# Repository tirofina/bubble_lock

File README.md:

# Privacy Bubble Keyring

![Story page 1. 4:30 PM, Mom heads out for a walk. Her daughter calls from work: "Mom, where are you?" "At the park. Get back to work." Mom pushes away a GPS watch: "Am I a prisoner?" The daughter shows her the keyring instead: "Who sees my walks?" "No one. It only shows home or away. Press orange if you get lost."](docs/story/page-1.png)

![Story page 2. Two weeks later, the daughter's screen shows only "4:31 PM, Mom went out" and "5:36 PM, Mom came home." At 5:09 PM Mom stands at a fork in the park path: "I know this path..." At 5:13 PM the daughter gets a check-in: "4 min at the east fork. Try calling. View for 5 min," and Mom presses the orange PANIC button. On a park bench, Mom says "Your dad and I used to sit here." "I know." Location sharing turns off.](docs/story/page-2.png)

*The keyring's family story, pages 1 and 2.*

**Privacy by default. Help before the button.** A BLE keyring for an older parent who lives alone, built on the [oneM2M](https://www.onem2m.org) service layer and ETSI MEC.

Mobius4 oneM2M CSE (4.24.5 in test runs, 4.25.0 on the team server) | ETSI MEC Sandbox | Code Apache-2.0 | Docs and hardware CC BY 4.0 | 2026 oneM2M International Hackathon

| | |
|---|---|
| Hackster.io project | [Privacy Bubble: Help Before the Button](https://www.hackster.io/even-bubble-lock-is-rock/privacy-bubble-help-before-the-button-601c1d) |
| Demo video (under 5 minutes) | [Mom, Where Are You? on YouTube](https://www.youtube.com/watch?v=vOgl1aOGWl0) |
| Why oneM2M, feature by feature | [docs/oneM2M-why.md](docs/oneM2M-why.md) |
| Architecture, resource tree, protocols | [docs/architecture.md](docs/architecture.md) |

## What it does

A resident carries the keyring, her daughter acts as guardian, and a caregiver visits in the afternoon. The oneM2M CSE stores shared data and enforces access for every app. The integration service adds grants, consent and approvals. Together they enforce four rules:

1. **Presence by default.** The keyring reports presence and button presses over BLE to a Raspberry Pi Gateway, which writes them to the CSE. The guardian sees one coarse status: At Home, Moving or In Park.
2. **Devices on grant.** A command requires an active, time-bounded grant and completes when the device reports a matching readback of its physical output.
3. **Help before the button.** A routine model learns her usual walks. On an unusual evening, a Claude triage agent sends the guardian a check-in message before the resident presses PANIC.
4. **Location on approval.** Precise location remains encrypted and becomes visible to one recipient for one incident, for up to five minutes.

*The guardian's alert card shows the triage agent's 17:13 check-in, the PANIC press escalating the same alert at 17:18, and a five-minute location share. Captured live from a real Mobius4 CSE with simulated device positions.*

## Architecture

```mermaid
flowchart LR
  K["Keyring r26<br/>ESP32-S3, BLE"] -- "BLE, bonded" --> GW["Raspberry Pi Gateway<br/>SQLite outbox"]
  GW -- "oneM2M MQTT binding, HTTPS fallback<br/>TLS 1.3 mTLS" --> CSE["Mobius4 CSE<br/>AE, container, flexContainer,<br/>group, subscription, ACP"]
  CSE -- "m2m:sgn" --> APPS["Guardian, caregiver and<br/>operator apps"]
  CSE -- "m2m:sgn" --> AI["Routine AE and triage AE<br/>MCP servers, Claude Code"]
  IPE["oneM2M MEC IPE<br/>on mep1, moves to mep2"] -- "oneM2M" --> CSE
  MEC["ETSI MEC Sandbox<br/>MEC011, 012, 013, 021"] --- IPE
  FL["Federated learning<br/>coordinator and workers"] -- "oneM2M" --> CSE
```

| oneM2M feature | Use here |
|---|---|
| accessControlPolicy | Every app, the MEC IPE and the AI agent are originators with narrow rights; each client certificate maps to one originator |
| Subscription and notification | One write notifies every subscribed app |
| Group and fanOutPoint | One UPDATE reaches every member keyring, with a result per member |
| SDT (TS-0023) and flexContainer | Device state is a `binarySwitch` (`cod:binSh`), found by `cnd` discovery; the keyring maps to `deviceServiceButton` with `pushButton` and `battery` ([model](docs/keyring-sdt-model.md)) |
| container and contentInstance | Immutable observations, receipts and incidents with an expiry |
| IPE | MEC013 Location, MEC012 RNIS and MEC021 events become oneM2M resources |

We map the edge layout to deployment option B of oneM2M TR-0077: the CSE and the MEC platform run on separate edge nodes.

## Results

Local runs use real Mobius4 processes (4.24.5, and 4.25.0 for the access-control matrix); the team server runs Mobius4 4.25.0. Every receipt identifies its simulated components. `npm run verify` passes 13 steps with 686 tests ([log](docs/verification/2026-11-22/results.json)).

| What | Result | Setup | Receipt |
|---|---|---|---|
| Keyring → Pi → Mobius4 | 35 real BLE observations stored and read back; 15/15 delivered over HTTPS during a broker outage | Real hardware | [pi-cse](keyring/evidence/2026-11-10-pi-cse/README.md) |
| Command with readback | LED ON and OFF commands settled after GPIO readback arrived through a CSE notification | Real hardware | [LED](keyring/evidence/2026-11-11-scoped-feather-led/receipt.json) |
| PANIC to three apps | 10–12 ms, 19/19 checks passed | Real CSE, emulated keyrings | [multiapp](docs/verification-evidence/2026-11-19/multiapp-real-cse.json) |
| One tap, three keyrings | `fopt` returned 2004, 2004 and 4103; retry targeted the member with 4103; 27/27 checks passed | Real CSE | [group command](docs/verification-evidence/2026-11-19/group-command-real-cse.json) |
| MQTT first, HTTPS when needed | All 509 observations arrived across 4 fault conditions | Real Gateway daemon | [protocol matrix](docs/verification-evidence/2026-11-19/protocol-matrix-real-cse.json) |
| Access-control matrix | 838/838 cases passed for six roles and six operations, including subscription creation and revocation | Mobius4 4.25.0 | [acp](docs/verification-evidence/2026-11-21/acp-real-cse.json), [location privacy](docs/verification-evidence/2026-11-21/location-privacy-real-cse.json) |
| Identity bound to ACP | 918/918 security cases passed; a forged originator received 4103 | Two real CSEs, real PKI | [acp-mtls](docs/verification-evidence/2026-11-19/acp-mtls-real-cse.json) |
| CSE handover | 30 handovers between two hosts preserved all 2,337 observations; p95 interruption was 978.4 ms; an unapproved originator received 4103 after every handover | Mobius4 4.25.0 on a PC and on a VM | [two hosts](docs/verification-evidence/2026-11-23/handover-two-host-real-cse.json), [one host](docs/verification-evidence/2026-11-19/handover-auto-real-cse.json) |
| MEC IPE | 33/33 checks passed on the real ETSI MEC Sandbox; relocation from mep1 to mep2 passed 25/25 checks and preserved every event | Real sandbox, scripted movement | [sandbox](docs/verification-evidence/2026-11-20/mec-ipe-sandbox.json), [day of care](docs/verification-evidence/2026-11-20/mec-day-of-care.json) |
| Check-in before PANIC | Across 6 synthetic walks: 0 false alarms, 0 missed events and a 265 s lead for the fork anomaly; the five-minute dwell baseline produced 12 false alarms | Real sandbox and CSE, synthetic walks | [triage](docs/verification-evidence/2026-11-20/anomaly-triage.json) |
| Federated learning | Macro-F1 reached 0.9394 versus 0.9479 for centralized training; raw data stayed local; the team server CSE completed 6 rounds | Real CSE, synthetic data | [local](docs/verification-evidence/2026-11-19/fl-onem2m-real-cse.json), [server](docs/verification-evidence/2026-11-20/fl-server-cse.json) |
| Team server CSE | The sandbox IPE wrote MEC locations over mTLS and passed all 11 checks reached during the run; the receipt records the remaining walk, RNIS, renewal and teardown checks as pending | Real sandbox, real server CSE | [server IPE](docs/verification-evidence/2026-11-20/mec-ipe-server-cse.json) |

Per-package notes are in [docs/rubric-work](docs/rubric-work), and every receipt is in [docs/verification-evidence](docs/verification-evidence).

## Hardware

| Part | Details |
|---|---|
| Keyring r26 | 4-layer ESP32-S3 board with 47 factory-assembled top-side parts, 1.54-inch ST7789 LCD, confirm and PANIC buttons, and a 1,000 mAh Li-Po. Gerber, BOM, CPL and KiCad project: [keyring/pcb/r26](keyring/pcb/r26/README.md) |
| Case | 11-part PLA print with STEP, STL and 3MF files and an assembly guide: [keyring/case/r26](keyring/case/r26/README.md) |
| Gateway | Raspberry Pi Zero 2 W with BlueZ: [raspberry-pi-gateway](keyring/raspberry-pi-gateway/README.md) |
| Bench keyring | Adafruit Feather ESP32 V2 for the command path: [feather_probe](keyring/firmware/feather_probe/README.md) |
| Full design | r18, with fuel gauge, accelerometer, charger and audio: [keyring/pcb/r18](keyring/pcb/r18/README.md) |

The r26 firmware (`keyring_r26_front_st7789` in [platformio.ini](keyring/firmware/platformio.ini)) and its bring-up guide ([R26_BRING_UP.md](keyring/pcb/R26_BRING_UP.md)) are in this repository.

## Quick start

Requires Node.js 22.19 or newer, Python 3.11 or newer, and OpenSSL. On Windows, clone with LF line endings so that the oneM2M XSD hashes match.

```powershell
git clone -c core.autocrlf=false https://github.com/tirofina/bubble_lock
cd bubble_lock
$env:PYTHON = (py -3 -c "import sys; print(sys.executable)")   # Linux: export PYTHON=python3
npm run setup     # installs pc-mobius, web-dashboard and the Python test environment
npm run verify    # 13 steps: unit tests, XSD closure, contracts, oneM2M dry-run, demo, replay, web build
```

Run the demo, event server, and dashboard in three terminals:

```powershell
npm run demo                  # writes pc-mobius/receipts/integration-demo.jsonl
$env:RECEIPT_FILE = (Resolve-Path 'pc-mobius/receipts/integration-demo.jsonl').Path
npm run events                # SSE event server on 127.0.0.1:4174
npm run dashboard             # http://127.0.0.1:5173
```

## Real Mobius4 and ETSI MEC Sandbox runs

Get [Mobius4](https://github.com/IoTKETI/mobius4) 4.24.5 (`git checkout v4.24.5`, `npm ci`) and set `MOBIUS4_ROOT`. Run PostgreSQL 17 with PostGIS and write `.local/postgres/connection.json` with `host`, `port`, `user`, `password` and `database`. The CORE contract runs against a CSE started by `pc-mobius/scripts/start-mobius4-test.ps1`; every other runner starts its own CSE processes and writes a JSON receipt.

| Result | Command |
|---|---|
| CORE contract on one CSE | `node pc-mobius/scripts/run-contract.mjs` after `start-mobius4-test.ps1` |
| Group fan-out and SDT clients | `node pc-mobius/scripts/run-group-command-real.mjs` |
| MQTT / HTTPS matrix | `node pc-mobius/scripts/run-protocol-matrix-real.mjs` |
| Three apps on one CSE | `node pc-mobius/scripts/run-multiapp-real.mjs` |
| Identity bound to ACP | `node pc-mobius/scripts/run-acp-mtls-real.mjs` |
| CSE handover | `node pc-mobius/scripts/run-handover-auto-real.mjs --rounds 5` |
| Federated learning | `node pc-mobius/scripts/run-fl-onem2m-real.mjs` |
| MEC IPE, local simulator | `node pc-mobius/scripts/run-mec-ipe-real.mjs` |
| MEC IPE, real sandbox | `npm --prefix pc-mobius run integration:mec-ipe-sandbox` |
| Day of care, IPE relocation | `npm --prefix pc-mobius run integration:mec-day-of-care` |
| Check-in before PANIC | `node pc-mobius/scripts/run-anomaly-triage.mjs --agent=claude` (or `--agent=scripted`) |

The sandbox runs require a local ETSI MEC Sandbox; [deploy/mec-sandbox](deploy/mec-sandbox/README.md) records the installation step by step.

## Deployment

- **Raspberry Pi Gateway:** systemd service under its own user, with certificates in `/etc/privacy-bubble/tls`: [raspberry-pi-gateway](keyring/raspberry-pi-gateway/README.md).
- **Central server:** Mobius4 with PostgreSQL and PostGIS, the binarySwitch specialization (`prepare-specialization`) and the standard subscription procedure on Mobius4 4.25.0 ([CSE_SECURITY.md](pc-mobius/integration/CSE_SECURITY.md)). The stack also includes an MQTT broker with TLS 1.3 and per-Gateway ACLs ([dev stack](keyring/dev/mobius4/README.md)), the integration API ([Gateway registration](pc-mobius/integration/GATEWAY_REGISTRATION.md)) and web apps with an OIDC backend ([oidc-session.md](web-dashboard/docs/oidc-session.md)).
- **ETSI MEC Sandbox and the MEC IPE image:** [deploy/mec-sandbox](deploy/mec-sandbox/README.md).

Certificates, private keys, passkeys, databases and runtime state belong in git-ignored paths such as `.local/` and `/etc/privacy-bubble/`.

## Repository map

| Path | Contents |
|---|---|
| [`pc-mobius/`](pc-mobius/README.md) | Central Node.js package: oneM2M core (group fan-out, SDT adapter, Gateway bridge), integration service (API, policy, MEC IPE, handover, FL, routine model, MCP servers), contracts, runners and tests |
| [`keyring/`](keyring/README.md) | Device side: firmware, PCB r18 and r26, case, Raspberry Pi Gateway, dev CSE stack, hardware evidence |
| [`web-dashboard/`](web-dashboard/README.md) | Guardian, caregiver and operator apps (React, Vite) with an SSE and OIDC backend |
| [`deploy/mec-sandbox/`](deploy/mec-sandbox/README.md) | ETSI MEC Sandbox install record, day-of-care scenario, MEC IPE container image |
| [`contracts/keyring/`](contracts/keyring/README.md) | JSON Schema contracts shared by firmware and Gateway |
| [`tests/integration/`](tests/integration) | Cross-runtime tests: Python and Node TLS 1.3 mTLS, OIDC, Gateway API |
| [`docs/`](docs) | Architecture, oneM2M rationale, per-package notes, verification logs and receipts |

Detailed design notes and run records are in Korean: [development record](docs/development-completion.md), [integration contracts](docs/branch-integration.md), and the README of each package.

## License and team

Code: [Apache License 2.0](LICENSE). Documentation, images, evidence and hardware design files: [CC BY 4.0](LICENSE-docs). Third-party material keeps its own terms: [NOTICE](NOTICE).

Team "Even Bubble lock is rock" built this project for the 2026 oneM2M International Hackathon across four roles: PC-MOBIUS-CORE, PC-MOBIUS-INTEGRATION, KEYRING and WEB-DASHBOARD. The [Hackster.io project](https://www.hackster.io/even-bubble-lock-is-rock/privacy-bubble-help-before-the-button-601c1d) lists the team members. Questions and feedback: [GitHub issues](https://github.com/tirofina/bubble_lock/issues).

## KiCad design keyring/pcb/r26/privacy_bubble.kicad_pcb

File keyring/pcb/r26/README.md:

# Keyring PCB r26 (front-side assembly)

r26 is the board revision inside the demo keyrings of Privacy Bubble Keyring. It is a 4-layer, 1.0 mm board around an ESP32-S3-WROOM-1 module, derived from r25 with one change: R71 is removed and the LCD data/command line is routed directly. For the 2026 oneM2M International Hackathon we ordered 5 boards and had 2 of them factory-assembled on the top side only.

The hardware author's original notes (Korean) are in [README.ko.md](README.ko.md). The case and its assembly guide are in [keyring/case/r26](../../case/r26/README.md).

## What is on the demo boards

| Item | Value |
|---|---|
| Stackup | 4 copper layers, 1.0 mm, standard 0.3 mm vias |
| Top side | 47 parts in 25 BOM lines, all placed by the factory; 0 hand-soldered parts, 0 jumper wires |
| Back side | 89 optional parts left unpopulated ([DNP_LIST.csv](assembly/DNP_LIST.csv)) |
| r26 change | R71 symbol, footprint and silkscreen removed; LCD_DC runs from GPIO8 (U1 pad 12) to J3 pin 6 on a 0.15 mm top-layer trace, with 0 extra vias |
| Kept from r25 | Placement, power loops, decoupling, board outline, case mounting holes and port positions |
| Checks (hardware author, KiCad 10.0.3) | DRC 0, ERC 0, unconnected 0, schematic parity 0 ([validation_summary.json](checks/validation_summary.json)) |

### Four 0-ohm bypass resistors

R72 to R75 are YAGEO RC0805JR-070RL (LCSC C96345, 0805), four per board. They let the front-side build run without the back-side power circuits.

| Resistor | Connects | Bypasses |
|---|---|---|
| R72 | VBAT to SYS_LIMIT | U3 charge and power path, U11 main switch |
| R73 | VBAT to PWR_SW (slide switch ON) | U10 undervoltage control |
| R74 | REG_EN (slide switch COM) to REG_READY (U4 EN) | U17 supply supervisor |
| R75 | +3V3 to AUX3V3 | U13 auxiliary power switch |

To populate a back-side circuit, first remove the bypass resistor that covers it. A full back-side build removes all four ([BYPASS_CONFIGURATION.csv](assembly/BYPASS_CONFIGURATION.csv)).

### Connections used by the demo firmware

| Function | Pins |
|---|---|
| Battery | J2 (check polarity first); DTP803040 1000 mAh, charged in an external 1-cell charger. USB-C charging, temperature and undervoltage circuits stay idle on this build, and USB-C carries ESP32 USB data. |
| Power switch | J9.1 ON, J9.2 COM, J9.3 OFF/GND |
| LCD (1.54 inch 240x240 ST7789) | MOSI GPIO38, SCK GPIO39, CS GPIO18, DC GPIO8, RESET GPIO43, backlight GPIO2 (HIGH off, LOW on) |
| Buttons | Confirm GPIO6, PANIC GPIO7, LOW when pressed |
| USB | D- GPIO19, D+ GPIO20, USB console. UART0 TX logging stays off because GPIO43 is the LCD reset. |
| Idle in the demo firmware | Audio, sensors, microSD, fuel gauge and the MAIN/AUX FAULT logic |

LCD harness (JST SH 8-pin) from the module labels to J3:

| LCD label | GND | VCC | SCL | SDA | RST | DC | CS | BL |
|---|---|---|---|---|---|---|---|---|
| r26 J3 pin | 2 | 1 | 4 | 3 | 7 | 6 | 5 | 8 |

Firmware build profiles, first power-on and over-the-air updates: [R26_BRING_UP.md](../R26_BRING_UP.md) and [R26_OTA.md](../../firmware/R26_OTA.md).

## Files

| Path | Contents |
|---|---|
| `privacy_bubble.kicad_pro`, `.kicad_sch`, `.kicad_pcb`, `.kicad_dru`, `fp-lib-table`, `sym-lib-table`, `Release.kicad_sym` | KiCad 10 project |
| `Sourced_4L.pretty/`, `Sourced.pretty/`, `HandSolder.pretty/`, `3dmodels/`, `sourced_cad/` | Footprints and 3D models; third-party terms in [NOTICE](../../../NOTICE) |
| [`fabrication/privacy_bubble_r26_4L_front_assembly_gerber_drill.zip`](fabrication/privacy_bubble_r26_4L_front_assembly_gerber_drill.zip) | Gerber and drill: 4 copper layers, masks and silkscreens on both sides, outline, top paste, PTH and NPTH drill |
| [`assembly/BOM_JLCPCB.csv`](assembly/BOM_JLCPCB.csv), [`assembly/CPL_JLCPCB.csv`](assembly/CPL_JLCPCB.csv) | Top-side assembly files with LCSC part numbers; quantities are per board |
| [`assembly/POPULATION_BY_REFERENCE.csv`](assembly/POPULATION_BY_REFERENCE.csv) | Populated or unpopulated, per reference |
| [`assembly/FIRMWARE_PIN_MAP.csv`](assembly/FIRMWARE_PIN_MAP.csv) | ESP32-S3 pads, nets and GPIOs used by the r26 firmware |
| `checks/validation_summary.json`, `drc_final.json`, `erc_final.json` | Hardware author's checks, KiCad 10.0.3 |
| `checks/drc_r26_label_2026-11-20.json`, `erc_r26_label_2026-11-20.json` | Re-run after the label update below, KiCad 10.0.4 |
| [`3d/r26_top_assembly.step`](3d/r26_top_assembly.step) | Board as assembled (top side) |
| [`3d/r26_aux_optional.step`](3d/r26_aux_optional.step) | Board with the optional AUX parts, for enclosure checks |
| [`exports/r26-schematic.pdf`](exports/r26-schematic.pdf) | Schematic |
| [`exports/r26-board-top.png`](exports/r26-board-top.png) | Top-side render |
| [`exports/r26-board-bottom-full-design.png`](exports/r26-board-bottom-full-design.png) | Bottom render of the full design; on the demo boards these 89 back-side parts stay unpopulated |

A KiCad XML netlist is easy to regenerate with `kicad-cli sch export netlist --format kicadxml privacy_bubble.kicad_sch`; it records the absolute path of the machine that exports it, so the repository leaves it out.

## Label update on 2026-11-20

The title blocks still named older revisions, so we changed three text fields to r26. Circuits, footprints, copper, masks, silkscreen and drill data stay the same, and the Gerber zip is the hardware author's original.

| File | Field | Before | After |
|---|---|---|---|
| `privacy_bubble.kicad_pcb` | title block rev | r19 / standard vias | r26 / direct LCD DC, front-side assembly |
| `privacy_bubble.kicad_sch` | title block rev | r17 edge ports / two-layer layout in progress | r26 / direct LCD DC, front-side assembly |
| `privacy_bubble.kicad_sch` | comment 1 | R16/R17/J8 removed; D2/R18 retained; 3D views updated | R71 removed; LCD_DC wired directly from GPIO8 to J3.6 |

| File | SHA-256 before (equal to validation_summary.json) | SHA-256 after |
|---|---|---|
| `privacy_bubble.kicad_pcb` | `3c408eef457f7f8830f5e8cf06486eea775e83996467143cab9025f8d674c1ef` | `2f1782920fe6bb1137ad30dc8b9f60af697f21621363e861de8cd5ab4229f0f4` |
| `privacy_bubble.kicad_sch` | `325c5987df2d07763a71aed6f76833c1f18a5b041ecb8c4495e2a1bf22ffe083` | `cce052aa005f6ac1cde41344dfae172f60b53c5b6fa131db039f051e661b30e7` |

Re-run with `kicad-cli` 10.0.4, errors and warnings included: DRC 0 violations and 0 unconnected items, ERC 0 violations.

## Build one

1. Order the board from the Gerber zip (4 layers, 1.0 mm) with top-side assembly from the BOM and CPL.
2. Print and assemble the case: [keyring/case/r26](../../case/r26/README.md).
3. Flash `keyring_r26_front_st7789` and pair the keyring with the Raspberry Pi Gateway: [R26_BRING_UP.md](../R26_BRING_UP.md).

## License

Project-authored design files in this folder: CC BY 4.0 ([LICENSE-docs](../../../LICENSE-docs)). KiCad library parts and supplier models keep their own terms ([NOTICE](../../../NOTICE)).

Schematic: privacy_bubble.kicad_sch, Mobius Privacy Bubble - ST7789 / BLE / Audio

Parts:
C1: 1uF 10V X7R; C_0603_1608Metric_Pad1.08x0.95mm_HandSolder_C1_HandSolder; MPN GRM188R71A105KA61D
C2: 10uF 10V X7R; C_0805_2012Metric_Pad1.18x1.45mm_HandSolder_C2_HandSolder; MPN GRM21BR71A106KE51L
C3: 100nF 50V X7R; C_0603_1608Metric_Pad1.08x0.95mm_HandSolder_C3_HandSolder_C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; MPN C1608X7R1H104K080AA
C4: 4.7uF 10V X7R; C_0805_2012Metric_Pad1.18x1.45mm_HandSolder_C4_HandSolder; MPN GRM21BR71A475KA73L
C5: 10uF 10V X7R; C_0805_2012Metric_Pad1.18x1.45mm_HandSolder_C5_HandSolder; MPN GRM21BR71A106KE51L
C6: 4.7uF 10V X7R; C_0805_2012Metric_Pad1.18x1.45mm_HandSolder_C6_HandSolder; MPN GRM21BR71A475KA73L
C7: 100nF 50V X7R; C_0402_1005Metric_Pad0.74x0.62mm_HandSolder; MPN GRM155R71H104KE14D
C8: 10uF 10V X7R; C_0805_2012Metric_Pad1.18x1.45mm_HandSolder_C8_HandSolder; MPN GRM21BR71A106KE51L
C9: 22uF 16V X5R; C_0805_2012Metric_Pad1.18x1.45mm_HandSolder_C9_HandSolder; MPN GRM21BR61C226ME44L
C10: 22uF 16V X5R; C_0805_2012Metric_Pad1.18x1.45mm_HandSolder_C10_HandSolder; MPN GRM21BR61C226ME44L
C15: 100nF 50V X7R; C_0402_1005Metric_Pad0.74x0.62mm_HandSolder_C15_HandSolder; MPN GRM155R71H104KE14D
C16: 100nF 50V X7R; C_0402_1005Metric_Pad0.74x0.62mm_HandSolder_C16_HandSolder; MPN GRM155R71H104KE14D
C17: 10uF 10V X5R 20%; C_0603_1608Metric_Pad1.08x0.95mm_HandSolder_C17_HandSolder; MPN GRM188R61A106ME69D
C18: 100nF 50V X7R; C_0603_1608Metric_Pad1.08x0.95mm_HandSolder_C18_HandSolder; MPN C1608X7R1H104K080AA
C19: 10uF 10V X7R; C_0805_2012Metric_Pad1.18x1.45mm_HandSolder_C19_HandSolder; MPN GRM21BR71A106KE51L
C20: 100nF 50V X7R; C_0402_1005Metric_Pad0.74x0.62mm_HandSolder_C20_HandSolder; MPN GRM155R71H104KE14D
C21: 100nF 50V X7R; C_0603_1608Metric_Pad1.08x0.95mm_HandSolder_C21_HandSolder; MPN C1608X7R1H104K080AA
C22: 10uF 10V X7R; C_0805_2012Metric_Pad1.18x1.45mm_HandSolder_C22_HandSolder_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; MPN GRM21BR71A106KE51L
C23, C49: 10uF 10V X7R; Capacitor_SMD_C_0805_2012Metric; MPN GRM21BR71A106KE51L
C24: 100nF 50V X7R; C_0402_1005Metric_Pad0.74x0.62mm_HandSolder_C24_HandSolder; MPN GRM155R71H104KE14D
C25: 100nF 50V X7R; C_0402_1005Metric_Pad0.74x0.62mm_HandSolder_C25_HandSolder; MPN C1005X7R1H104K050BB
C26: 100nF 50V X7R; C_0402_1005Metric_Pad0.74x0.62mm_HandSolder_C26_HandSolder; MPN C1005X7R1H104K050BB
C27: 100nF 50V X7R; C_0402_1005Metric_Pad0.74x0.62mm_HandSolder_C27_HandSolder; MPN GRM155R71H104KE14D
C28: 10uF 10V X7R; C_0805_2012Metric_Pad1.18x1.45mm_HandSolder_C28_HandSolder; MPN GRM21BR71A106KE51L
C29: 100nF 50V X7R; C_0402_1005Metric_Pad0.74x0.62mm_HandSolder_C29_HandSolder; MPN GRM155R71H104KE14D
C30: 4.7nF 50V X7R 10%; C_0402_1005Metric; MPN GRM155R71H472KA01D
C31: 1nF 50V C0G; C_0402_1005Metric_Pad0.74x0.62mm_HandSolder_C31_HandSolder; MPN GRM1555C1H102JA01D
C32: 100nF 50V X7R; C_0402_1005Metric_Pad0.74x0.62mm_HandSolder_C32_HandSolder; MPN GRM155R71H104KE14D
C33: 22uF 16V X5R; C_0805_2012Metric_Pad1.18x1.45mm_HandSolder_C33_HandSolder; MPN GRM21BR61C226ME44L
C35: 100nF 50V X7R; C_0402_1005Metric_Pad0.74x0.62mm_HandSolder_C35_HandSolder; MPN GRM155R71H104KE14D
C36: 100nF 50V X7R; C_0402_1005Metric_Pad0.74x0.62mm_HandSolder_C36_HandSolder; MPN GRM155R71H104KE14D
C37: 330uF 6.3V polymer; CP_EIA-7343-31_Kemet-D_C37_HandSolder; MPN T520D337M006ATE025
C38: 1uF 10V X5R; C_0402_1005Metric_Pad0.74x0.62mm_HandSolder_C38_HandSolder; MPN CL05A105KP5NNNC
C39: 1uF 10V X5R; C_0402_1005Metric_Pad0.74x0.62mm_HandSolder_C39_HandSolder; MPN CL05A105KP5NNNC
C40: 1uF 10V X5R; C_0402_1005Metric_Pad0.74x0.62mm_HandSolder_C40_HandSolder; MPN CL05A105KP5NNNC
C41: 1uF 10V X5R; C_0402_1005Metric_Pad0.74x0.62mm_HandSolder_C41_HandSolder; MPN CL05A105KP5NNNC
C42: 1uF 10V X5R; C_0402_1005Metric_Pad0.74x0.62mm_HandSolder_C42_HandSolder; MPN CL05A105KP5NNNC
C43: 1uF 10V X5R; C_0402_1005Metric_Pad0.74x0.62mm_HandSolder_C43_HandSolder; MPN CL05A105KP5NNNC
C44: 470nF 10V X5R; C_0402_1005Metric; MPN GRM155R61A474KE15D
C45: 2.2uF 10V X5R; C_0603_1608Metric; MPN CL10A225KP8NNNC
C46: 680uF 6.3V polymer; CP_EIA-7343-43_Kemet-X_C46_HandSolder; MPN T530X687M006ATE010
C47: 680uF 6.3V polymer; CP_EIA-7343-43_Kemet-X_C47_HandSolder; MPN T530X687M006ATE010
C48: 100nF 50V X7R; C_0402_1005Metric_Pad0.74x0.62mm_HandSolder_C48_HandSolder; MPN GRM155R71H104KE14D
C50: 470uF 6.3V polymer; CP_EIA-7343-31_Kemet-D_C50_HandSolder; MPN T520D477M006ATE025
D1: PMEG2010ER flyback; D_Diode_SMD_Nexperia_CFP3_SOD-123W_D1_HandSolder; MPN PMEG2010ER,115
D2: CHARGE LED; LED_0603_1608Metric_Pad1.05x0.95mm_HandSolder_D2_HandSolder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; MPN LTST-C190KRKT
J1: USB-C USB2.0; USB_C_Receptacle_HRO_TYPE-C-31-M-12_J1_HandSolder; MPN TYPE-C-31-M-12
J2: BATTERY DTP803040; Connector_JST_JST_PH_S2B-PH-SM4-TB_1x02-1MP_P2.00mm_Horizon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; MPN S2B-PH-SM4-TB(LF)(SN)
J3: ST7789 HARNESS; Connector_JST_JST_SH_SM08B-SRSS-TB_1x08_1MP_P1.00mm_Horizon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; MPN SM08B-SRSS-TB(LF)(SN)
J4: SPEAKER WIRE SOLDER; SolderWire-0.1sqmm_1x02_P3.6mm_D0.4mm_OD1mm
J5: NTC DIRECT SOLDER; SolderWire-0.1sqmm_1x02_P3.6mm_D0.4mm_OD1mm
J6: MOTOR WIRE SOLDER; SolderWire-0.5sqmm_1x02_P4.6mm_D0.9mm_OD2.1mm
J7: UART DEBUG; DebugPads_1x04_P1.27; not fitted
J9: POWER SWITCH WIRES; Connector_Wire_SolderWire-0.127sqmm_1x03_P3.7mm_D0.48mm_OD1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
J10: microSD DM3AT-SF-PEJM5; microSD_HC_Hirose_DM3AT-SF-PEJM5_J10_HandSolder; MPN DM3AT-SF-PEJM5
J11: 3.5mm stereo output; AUDIO-SMD_PJ-320D; MPN PJ-320D-4A
L1: 2.2uH XFL4020; Inductor_SMD_L_Coilcraft_XxL4020_L1_HandSolder; MPN XFL4020-222MEC
NT1: AGND STAR; NetTie_NetTie-2_SMD_Pad0.5mm
NT2: HEADPHONE ANALOG STAR; NetTie-2_SMD_Pad0.5mm; MPN PCB copper
Q1: AO3400A; SOT-23_Handsoldering_Q1_HandSolder; MPN AO3400A
Q2: 2N7002; SOT-23_Handsoldering_Q2_HandSolder; MPN 2N7002
Q3: AO3401A; SOT-23_Handsoldering_Q3_HandSolder; MPN AO3401A
Q4: 2N7002; SOT-23_Handsoldering_Q4_HandSolder; MPN 2N7002
R1: 100k 1%; R_0402_1005Metric_Pad0.72x0.64mm_HandSolder_R1_HandSolder; MPN RC0402FR-07100KL
R2: 10k 1%; R_0402_1005Metric_Pad0.72x0.64mm_HandSolder_R2_HandSolder; MPN RC0402FR-0710KL
R3: 4.7k 1%; R_0402_1005Metric_Pad0.72x0.64mm_HandSolder_R3_HandSolder; MPN RC0402FR-074K7L
R4: 4.7k 1%; R_0402_1005Metric_Pad0.72x0.64mm_HandSolder_R4_HandSolder; MPN RC0402FR-074K7L
R5: 47k 1%; R_0402_1005Metric_Pad0.72x0.64mm_HandSolder_R5_HandSolder; MPN RC0402FR-0747KL
R6: 47k 1%; R_0402_1005Metric_Pad0.72x0.64mm_HandSolder_R6_HandSolder; MPN RC0402FR-0747KL
R7: 5.1k 1%; R_0402_1005Metric_Pad0.72x0.64mm_HandSolder_R7_HandSolder; MPN RC0402FR-075K1L
R8: 5.1k 1%; R_0402_1005Metric_Pad0.72x0.64mm_HandSolder_R8_HandSolder; MPN RC0402FR-075K1L
R9: 33R 1%; R_0402_1005Metric_Pad0.72x0.64mm_HandSolder_R9_HandSolder; MPN RC0402FR-0733RL
R10: 33R 1%; R_0402_1005Metric_Pad0.72x0.64mm_HandSolder_R10_HandSolder; MPN RC0402FR-0733RL
R11: 100k 1%; R_0402_1005Metric_Pad0.72x0.64mm_HandSolder_R11_HandSolder; MPN RC0402FR-07100KL
R12: 4.53k 1%; R_0402_1005Metric_Pad0.72x0.64mm_HandSolder_R12_HandSolder; MPN RC0402FR-074K53L
R13: 3.57k 1%; R_0402_1005Metric_Pad0.72x0.64mm_HandSolder_R13_HandSolder; MPN RC0402FR-073K57L
R14: 1.50k 1%; R_0402_1005Metric_Pad0.72x0.64mm_HandSolder_R14_HandSolder; MPN RC0402FR-071K5L
R15: 69.8k 1%; R_0402_1005Metric_Pad0.72x0.64mm_HandSolder_R15_HandSolder; MPN RC0402FR-0769K8L
R18: 2.2k 1%; R_0402_1005Metric_Pad0.72x0.64mm_HandSolder_R18_HandSolder; MPN RC0402FR-072K2L
R19: 100R 1%; R_0402_1005Metric_Pad0.72x0.64mm_HandSolder_R19_HandSolder; MPN RC0402FR-07100RL
R20: 10k 1%; R_0402_1005Metric_Pad0.72x0.64mm_HandSolder_R20_HandSolder; MPN RC0402FR-0710KL
R31: 33R 1%; R_0402_1005Metric_Pad0.72x0.64mm_HandSolder_R31_HandSolder; MPN RC0402FR-0733RL
R32: 33R 1%; R_0402_1005Metric_Pad0.72x0.64mm_HandSolder_R32_HandSolder; MPN RC0402FR-0733RL
R33: 47k 1%; R_0402_1005Metric_Pad0.72x0.64mm_HandSolder_R33_HandSolder; MPN RC0402FR-0747KL
R34: 47k 1%; R_0402_1005Metric_Pad0.72x0.64mm_HandSolder_R34_HandSolder; MPN RC0402FR-0747KL
R35: 100k 1%; Resistor_SMD_R_0402_1005Metric; MPN RC0402FR-07100KL
R36: 33R 1%; R_0402_1005Metric_Pad0.72x0.64mm_HandSolder_R36_HandSolder; MPN RC0402FR-0733RL
R37: 33R 1%; R_0402_1005Metric_Pad0.72x0.64mm_HandSolder_R37_HandSolder_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; MPN RC0402FR-0733RL
R38: 33R 1%; R_0402_1005Metric_Pad0.72x0.64mm_HandSolder_R38_HandSolder; MPN RC0402FR-0733RL
R39: 100k 1%; R_0402_1005Metric_Pad0.72x0.64mm_HandSolder_R39_HandSolder; MPN RC0402FR-07100KL
R40: 100k 1%; R_0402_1005Metric_Pad0.72x0.64mm_HandSolder_R40_HandSolder; MPN RC0402FR-07100KL
R41: 100R 1%; R_0402_1005Metric_Pad0.72x0.64mm_HandSolder_R41_HandSolder; MPN RC0402FR-07100RL
R42: 100k 1%; R_0402_1005Metric_Pad0.72x0.64mm_HandSolder_R42_HandSolder; MPN RC0402FR-07100KL
R43: 100k 1%; R_0402_1005Metric_Pad0.72x0.64mm_HandSolder_R43_HandSolder; MPN RC0402FR-07100KL
R44: 100k 1%; R_0402_1005Metric_Pad0.72x0.64mm_HandSolder_R44_HandSolder; MPN RC0402FR-07100KL
R45, R46: 1M 1%; Resistor_SMD_R_0402_1005Metric; MPN RC0402FR-071ML
R47: 560k 1%; R_0402_1005Metric_Pad0.72x0.64mm_HandSolder_R47_HandSolder; MPN RC0402FR-07560KL
R48: 47k 1%; R_0402_1005Metric_Pad0.72x0.64mm_HandSolder_R48_HandSolder; MPN RC0402FR-0747KL
R49: 100k 1%; R_0402_1005Metric_Pad0.72x0.64mm_HandSolder_R49_HandSolder; MPN RC0402FR-07100KL
R50: 100k 1%; R_0402_1005Metric_Pad0.72x0.64mm_HandSolder_R50_HandSolder; MPN RC0402FR-07100KL
R51: 100k 1%; R_0402_1005Metric_Pad0.72x0.64mm_HandSolder_R51_HandSolder; MPN RC0402FR-07100KL
R52: 61.9k 1%; R_0402_1005Metric_Pad0.72x0.64mm_HandSolder_R52_HandSolder; MPN RC0402FR-0761K9L
R53: 100k 1%; R_0402_1005Metric_Pad0.72x0.64mm_HandSolder_R53_HandSolder; MPN RC0402FR-07100KL
R54: 57.6k 1%; R_0402_1005Metric_Pad0.72x0.64mm_HandSolder_R54_HandSolder; MPN RC0402FR-0757K6L
R55: 1M 1%; R_0402_1005Metric_Pad0.72x0.64mm_HandSolder_R55_HandSolder; MPN RC0402FR-071ML
R56: 100k 1%; R_0402_1005Metric_Pad0.72x0.64mm_HandSolder_R56_HandSolder; MPN RC0402FR-07100KL
R57: 100k 1%; R_0402_1005Metric_Pad0.72x0.64mm_HandSolder_R57_HandSolder; MPN RC0402FR-07100KL
R58: 100k 1%; R_0402_1005Metric; MPN RC0402FR-07100KL
R59: 133k 1%; R_0402_1005Metric; MPN RC0402FR-07133KL
R60: 100R 1% 0.5W; R_0805_2012Metric_Pad1.20x1.40mm_HandSolder_R60_HandSolder; MPN ERJP06F1000V
R61: 0.1R 1% 0.125W; R_0805_2012Metric_Pad1.20x1.40mm_HandSolder_R61_HandSolder; MPN RL0805FR-070R1L
R62: 100k 1%; R_0402_1005Metric_Pad0.72x0.64mm_HandSolder_R62_HandSolder; MPN RC0402FR-07100KL
R63: 47k 1%; R_0402_1005Metric_Pad0.72x0.64mm_HandSolder_R63_HandSolder; MPN RC0402FR-0747KL
R64: 47k 1%; R_0402_1005Metric_Pad0.72x0.64mm_HandSolder_R64_HandSolder; MPN RC0402FR-0747KL
R65: 47k 1%; R_0402_1005Metric_Pad0.72x0.64mm_HandSolder_R65_HandSolder; MPN RC0402FR-0747KL
R66: 47k 1%; R_0402_1005Metric_Pad0.72x0.64mm_HandSolder_R66_HandSolder; MPN RC0402FR-0747KL
R67: 47k 1%; R_0402_1005Metric_Pad0.72x0.64mm_HandSolder_R67_HandSolder; MPN RC0402FR-0747KL
R68: 33R 1%; R_0402_1005Metric_Pad0.72x0.64mm_HandSolder_R68_HandSolder; MPN RC0402FR-0733RL
R69: 220R 1%; R_0603_1608Metric_Pad0.98x0.95mm_HandSolder_R69_HandSolder; MPN RC0603FR-07220RL
R72, R73, R74, R75: 0R; R_0805_2012Metric_Pad1.20x1.40mm_HandSolder_R71_HandSolder; MPN RC0805JR-070RL
SW1: PANIC; Button_Switch_SMD_SW_SPST_PTS810; MPN PTS810SJK250SMTRLFS
SW2: CONFIRM; Button_Switch_SMD_SW_SPST_PTS810; MPN PTS810SJK250SMTRLFS
SW3: RESET; Button_Switch_SMD_SW_SPST_PTS810; MPN PTS810SJK250SMTRLFS
SW4: BOOT; Button_Switch_SMD_SW_SPST_PTS810; MPN PTS810SJK250SMTRLFS
TP1: VBUS; TestPoint_TestPoint_Pad_D1.0mm
TP2: VBAT; TestPoint_TestPoint_Pad_D1.0mm
TP3: SYS; TestPoint_TestPoint_Pad_D1.0mm
TP4: +3V3; TestPoint_TestPoint_Pad_D1.0mm
TP5: GND; TestPoint_TestPoint_Pad_D1.0mm
TP6: PGOOD_N; TestPoint_TestPoint_Pad_D1.0mm
TP7: CHG_N; TestPoint_TestPoint_Pad_D1.0mm
U1: ESP32-S3-WROOM-1-N16R8; RF_Module_ESP32-S3-WROOM-1_JLC030_CaseRelief_r24_U1; MPN ESP32-S3-WROOM-1-N16R8
U3: BQ24074RGTR; Package_DFN_QFN_VQFN-16-1EP_3x3mm_P0.5mm_EP1.6x1.6mm; MPN BQ24074RGTR
U4: TPS63001DRCR; Package_SON_Texas_DRC0010J_ThermalVias_JLC030; MPN TPS63001DRCR
U6: LIS2DW12TR; Package_LGA_LGA-12_2x2mm_P0.5mm; MPN LIS2DW12TR
U7: MAX17048G+; Package_DFN_QFN_TDFN-8-1EP_2x2mm_P0.5mm_EP0.8x1.2mm; MPN MAX17048G+
U8: MAX98357AETE+; Package_DFN_QFN_TQFN-16-1EP_3x3mm_P0.5mm_EP1.23x1.23mm; MPN MAX98357AETE+
U9: USBLC6-2SC6; SOT-23-6_Handsoldering_U9_HandSolder; MPN USBLC6-2SC6
U10: TLV6700DDCR; SOT-23-6_Handsoldering_U10_HandSolder; MPN TLV6700DDCR
U11: TPS2553DBVR; SOT-23-6_Handsoldering_U11_HandSolder; MPN TPS2553DBVR
U12: TLV3012BIDBVR; SOT-23-6_Handsoldering_U12_HandSolder; MPN TLV3012BIDBVR
U13: TPS2553DBVR; SOT-23-6_Handsoldering_U13_HandSolder; MPN TPS2553DBVR
U15: INA219BIDCNR; SOT-23-8_Handsoldering_U15_HandSolder; MPN INA219BIDCNR
U16: MAX9850ETI+; TQFN-28-1EP_5x5mm_P0.5mm_EP3.25x3.25mm_SilkClearance_r23_U16; MPN MAX9850ETI+
U17: TPS3839G18DBZR; SOT-23_Handsoldering_U17_HandSolder; MPN TPS3839G18DBZR

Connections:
/+3V3: C2.1, C3.1, C15.1, C16.1, C17.1, C19.1, C20.1, C32.1, C35.1, C36.1, C37.1, C38.1, C39.1, C40.1, C49.1, J3.1, J7.1, J10.4 (VDD), R1.1, R2.1, R3.1, R4.1, R5.1, R6.1, R33.1, R34.1, R56.1, R57.1, R61.2, R63.2, R64.2, R65.2, R66.2, R67.2, R75.1, TP4.1, U1.2 (3V3), U6.2 (CS), U6.3 (SA0), U6.9 (VDD), U6.10 (VDDIO), U13.1 (IN), U15.2 (IN-), U15.4 (VS), U16.4 (DVDD), U16.17 (AVDD), U16.26 (PVDD)
/ACCEL_INT: U1.10 (IO17), U6.12 (INT1)
/AMP_EN: Q4.3 (D), R39.1, U8.4 (SD_MODE)
/AMP_GAIN: R40.2, U8.2 (GAIN_SLOT)
/AMP_GATE: Q4.1 (G), R62.1, U1.9 (IO16)
/AUX3V3: C21.1, C22.1, C23.1, C33.1, D1.1 (K), J6.1, Q3.2 (S), R35.2, R39.2, R40.1, R75.2, U8.7 (VDD), U8.8 (VDD), U13.6 (OUT)
/AUX_EN: R58.1, U1.4 (IO4), U13.3 (EN)
/AUX_FAULT_N: R57.2, U13.4 (~FAULT)
/AUX_ILIM: R59.1, U13.5 (ILIM)
/BAT_TS: J5.1, R44.1, R46.1, U3.1 (TS)
/BOOT0: R2.2, SW4.1, U1.27 (IO0)
/BTN_CONFIRM: R6.2, SW2.1, U1.6 (IO6)
/BTN_PANIC: R5.2, SW1.1, U1.7 (IO7)
/CHG_DISABLE: Q2.3 (D), R49.2, U3.4 (~CE)
/CHG_ILIM: R13.1, U3.12 (ILIM)
/CHG_ISET: R12.1, U3.16 (ISET)
/CHG_ITERM: R14.1, U3.15 (ITERM)
/CHG_LED_A: D2.2 (A), R18.2
/CHG_N: D2.1 (K), TP7.1, U3.9 (~CHG)
/CHG_TMR: R15.1, U3.14 (TMR)
/GND: C1.2, C2.2, C3.2, C4.2, C5.2, C6.2, C8.2, C9.2, C10.2, C15.2, C16.2, C17.2, C18.2, C19.2, C20.2, C21.2, C22.2, C23.2, C24.2, C25.2, C26.2, C27.2, C28.2, C29.2, C30.2, C31.2, C32.2, C33.2, C35.2, C36.2, C37.2, C38.2, C40.2, C45.2, C46.2, C47.2, C48.2, C49.2, C50.2, J1.A1 (GND), J1.A12 (GND), J1.B1 (GND), J1.B12 (GND), J1.SH (SHIELD), J2.2, J3.2, J5.2, J7.2, J9.3, J10.6 (VSS), J10.SH (SHIELD), NT1.2, NT2.2, Q1.2 (S), Q2.2 (S), Q4.2 (S), R7.2, R8.2, R11.2, R12.2, R13.2, R14.2, R15.2, R42.2, R43.2, R45.2, R47.2, R50.2, R51.2, R52.2, R54.2, R58.2, R59.2, R62.2, SW1.2, SW2.2, SW3.2, SW4.2, TP5.1, U1.1 (GND), U1.40 (GND), U1.41 (GND), U3.8 (VSS), U3.17 (VSS), U4.3 (PGND), U4.7 (PS/SYNC), U4.11 (PGND), U6.6 (GND), U6.7 (RES_GND), U6.8 (GND), U7.1 (CTG), U7.4 (GND), U7.6 (QSTRT), U7.9 (EP_GND), U8.3 (GND), U8.11 (GND), U8.15 (GND)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
/HP_AGND: C39.2, C41.2, C42.2, C43.2, J11.1, J11.2, NT2.1, U16.9 (INR), U16.10 (INL), U16.14 (AGND), U16.29 (AGND)
/HP_C1N: C44.2, U16.23 (C1N)
/HP_C1P: C44.1, U16.25 (C1P)
/HP_L: J11.4, U16.19 (HPL)
/HP_MCLK: R68.2, U16.5 (MCLK)
/HP_MCLK_RAW: R68.1, U1.21 (IO13)
/HP_NREG: C42.1, U16.15 (NREG)
/HP_PREG: C43.1, U16.16 (PREG)
/HP_PVSS: C45.1, U16.20 (SVSS), U16.22 (PVSS)
/HP_R: J11.3, U16.18 (HPR)
/HP_REF: C41.1, U16.13 (REF)
/I2C_SCL: R4.2, U1.23 (IO21), U6.1 (SCL), U7.7 (SCL), U15.5 (SCL), U16.27 (SCL)
/I2C_SDA: R3.2, U1.22 (IO14), U6.4 (SDA), U7.8 (SDA), U15.6 (SDA), U16.28 (SDA)
/I2S_BCLK: R36.2, U8.16 (BCLK), U16.2 (BCLK)
/I2S_BCLK_RAW: R36.1, U1.34 (IO41)
/I2S_DOUT: R38.2, U8.1 (DIN), U16.3 (SDIN)
/I2S_DOUT_RAW: R38.1, U1.35 (IO42)
/I2S_LRCLK: R37.2, U8.14 (LRCLK), U16.1 (LRCLK)
/I2S_LRCLK_RAW: R37.1, U1.33 (IO40)
/LCD_BL_PWM: Q3.1 (G), R35.1, U1.38 (IO2)
/LCD_BL_RAW: Q3.3 (D), R60.1
/LCD_BL_SUPPLY: J3.8, R60.2
/LCD_CS: J3.5, R33.2, U1.11 (IO18)
/LCD_DC: J3.6, U1.12 (IO8)
/LCD_MOSI: J3.3, J10.3 (CMD), R32.2, R65.1
/LCD_MOSI_RAW: R32.1, U1.31 (IO38)
/LCD_RST: J3.7, R34.2, R69.2
/LCD_SCK: J3.4, J10.5 (CLK), R31.2
/LCD_SCK_RAW: R31.1, U1.32 (IO39)
/MAIN_FAULT_N: R56.2, U1.39 (IO1), U11.4 (~FAULT)
/MAIN_ILIM: R52.1, U11.5 (ILIM)
/MCU_EN: C1.1, R1.2, SW3.1, U1.3 (EN)
/PGOOD_N: TP6.1, U3.7 (~PGOOD)
/PWR_SW: J9.1, R20.2, R73.2
/REG_AGND: C7.2, NT1.1, U4.9 (GND)
/REG_EN: C24.1, J9.2, R43.1, R74.1, U11.3 (EN)
/REG_READY: R74.2, U4.6 (EN), U17.2 (~RESET)
/SD_CS: J10.2 (DAT3/CD), R63.1, U1.18 (IO10)
/SD_DAT1_PULL: J10.8 (DAT1), R66.1
/SD_DAT2_PULL: J10.1 (DAT2), R67.1
/SD_MISO: J10.7 (DAT0), R64.1, U1.19 (IO11)
/SPK_N: J4.2, U8.10 (OUTN)
/SPK_P: J4.1, U8.9 (OUTP)
/SW_L1: L1.1, U4.4 (L1)
/SW_L2: L1.2, U4.2 (L2)
/SYS: C5.1, C27.1, C29.1, R53.1, TP3.1, U3.10 (OUT), U3.11 (OUT), U11.1 (IN), U12.6 (V+)
/SYS_LIMIT: C8.1, C28.1, C46.1, C47.1, C48.1, C50.1, R19.1, R72.2, U4.5 (VIN), U11.6 (OUT), U17.3 (VDD)
/TEMP_COLD_SENSE: R46.2, R47.1, U10.4 (INB-)
/TEMP_HOT_SENSE: R44.2, R45.1, U10.3 (INA+)
/TEMP_OK: Q2.1 (G), R48.2, R50.1, U10.1 (OUTA), U10.6 (OUTB)
/UART_RX: J7.4, U1.36 (RXD0)
/UART_TX: J7.3, R69.1, U1.37 (TXD0)
/USB_500_EN: R11.1, U1.24 (IO47), U3.6 (EN1)
/USB_CC1: J1.A5 (CC1), R7.1
/USB_CC2: J1.B5 (CC2), R8.1
/USB_DM: J1.A7 (D-), J1.B7 (D-), R9.1, U9.3 (I/O2), U9.4 (I/O2)
/USB_DM_MCU: R9.2, U1.13 (USB_D-)
/USB_DP: J1.A6 (D+), J1.B6 (D+), R10.1, U9.1 (I/O1), U9.6 (I/O1)
/USB_DP_MCU: R10.2, U1.14 (USB_D+)
/USB_LIMIT_EN2: R51.1, U1.17 (IO9), U3.5 (EN2)
/UVLO_OK: R20.1, R55.1, U12.1 (OUT)
/UVLO_REF: C30.1, U12.4 (IN-), U12.5 (REF)
/UVLO_SENSE: C31.1, R53.2, R54.1, R55.2, U12.3 (IN+)
/VBAT: C6.1, C18.1, J2.1, R18.1, R72.1, R73.1, TP2.1, U3.2 (BAT), U3.3 (BAT), U7.2 (CELL), U7.3 (VDD)
/VBUS: C4.1, C25.1, C26.1, J1.A4 (VBUS), J1.A9 (VBUS), J1.B4 (VBUS), J1.B9 (VBUS), R48.1, R49.1, TP1.1, U3.13 (IN), U9.5 (VBUS), U10.5 (VDD)
/VIB_GATE: Q1.1 (G), R41.2, R42.1
/VIB_LOW: D1.2 (A), J6.2, Q1.3 (D)
/VIB_PWM: R41.1, U1.15 (IO3)
/VINA: C7.1, R19.2, U4.8 (VINA)
/VREG3V3: C9.1, C10.1, R61.1, U4.1 (VOUT), U4.10 (FB), U15.1 (IN+)

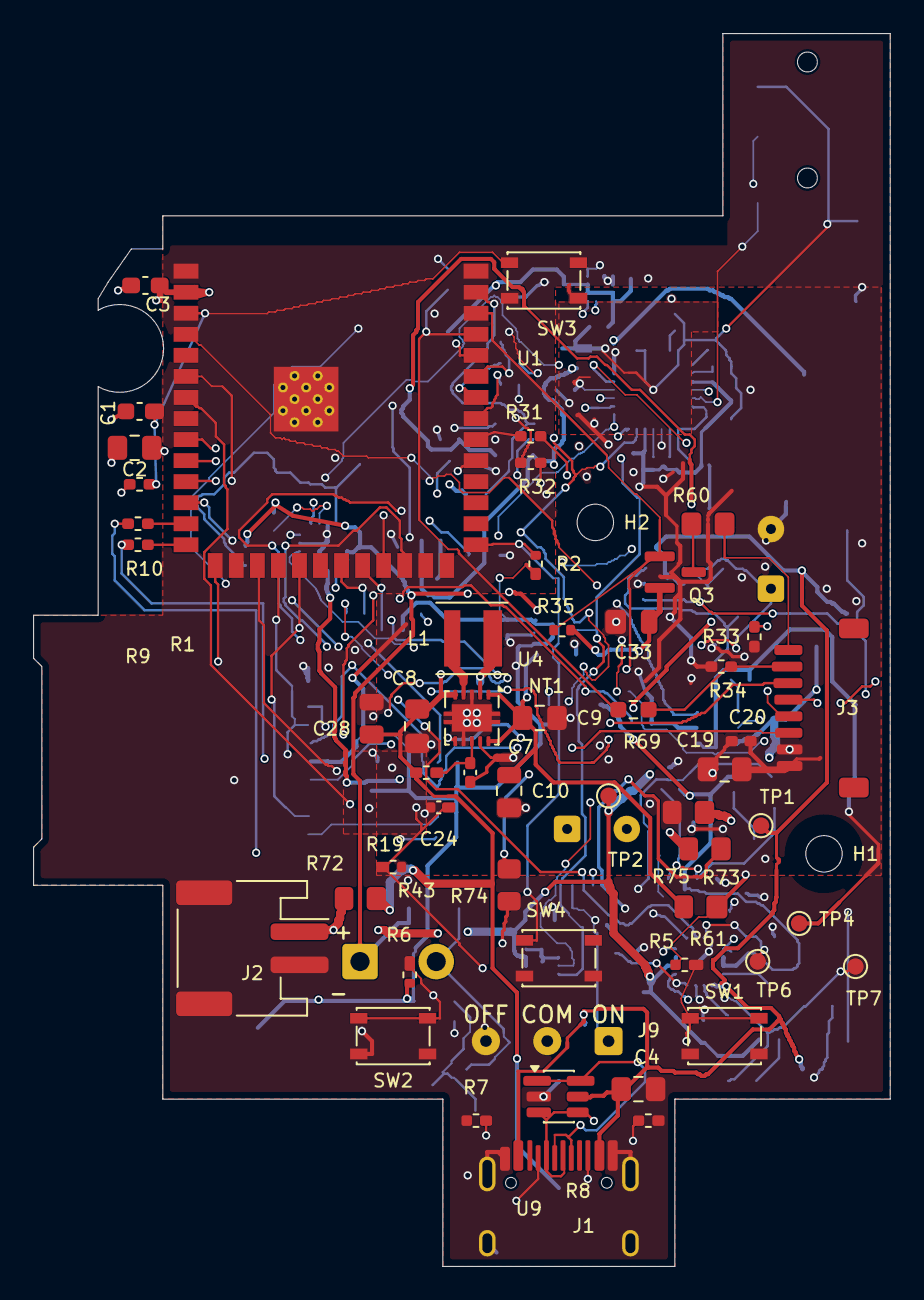
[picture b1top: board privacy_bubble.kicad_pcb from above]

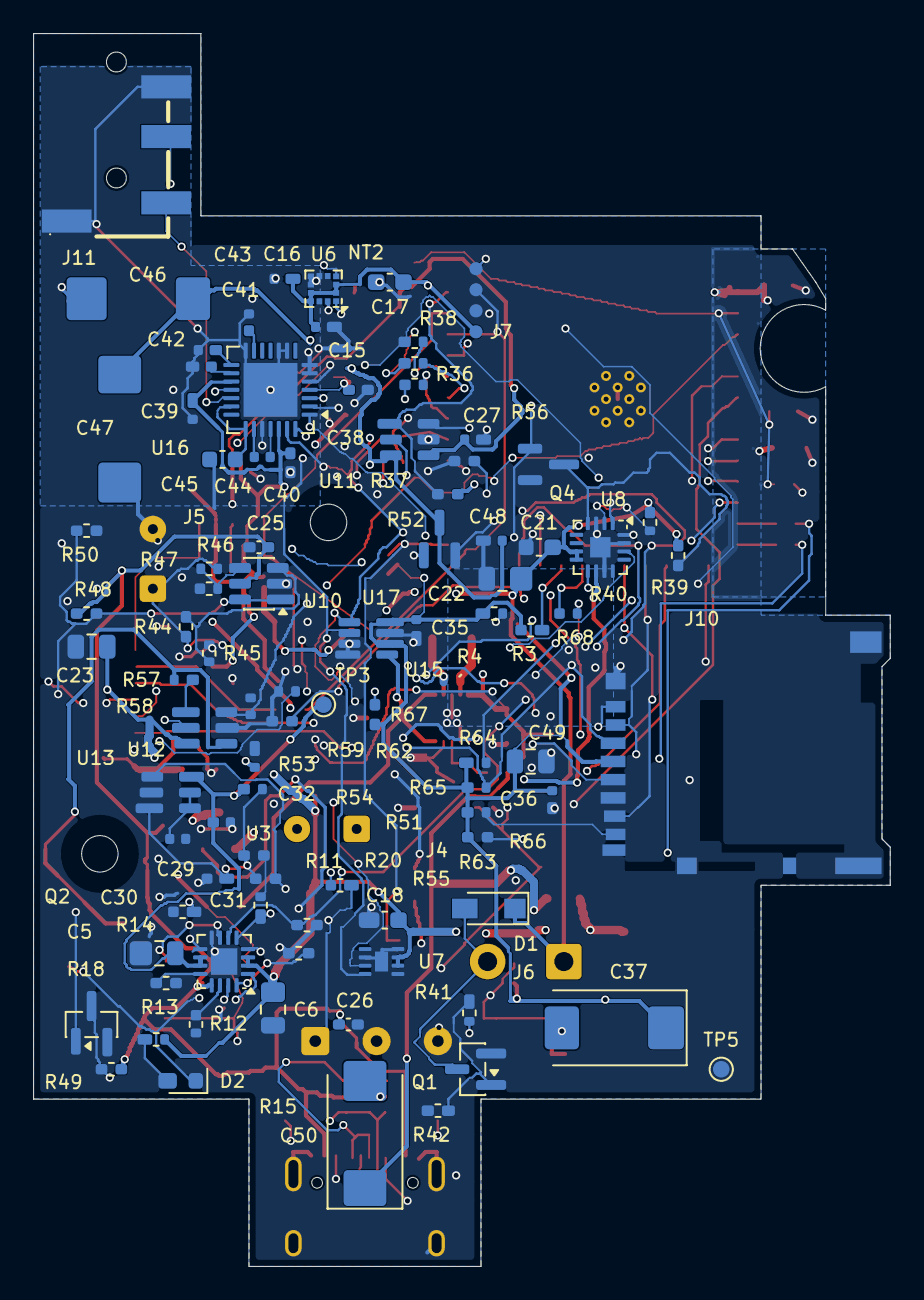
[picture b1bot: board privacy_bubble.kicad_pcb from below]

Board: 4 copper layers, 51.7 x 74.4 mm, 152 parts (96 on the bottom side), 91 nets.

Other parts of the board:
H1, H2: M2 / NPTH 2.2mm; MountingHole_2.2mm_M2

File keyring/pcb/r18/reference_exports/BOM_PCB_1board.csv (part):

MPN,Manufacturer,Quantity_per_PCB,References,Value,Footprints,Sides,Datasheet
GRM188R71A105KA61D,Murata,1,C1,1uF 10V X7R,HandSolder:C_0603_1608Metric_Pad1.08x0.95mm_HandSolder_C1_HandSolder,B,https://www.murata.com/en-global/products/productdetail?part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
GRM21BR71A106KE51L,Murata,8,C2 C5 C8 C19 C22 C23 C49 C28,10uF 10V X7R,HandSolder:C_0805_2012Metric_Pad1.18x1.45mm_HandSolder_C2_HandSolder | HandSolder:C_0805_2012Metric_Pad1.18x1.45mm_HandSolder_C5_HandSolder | HandSolder:C_0805_2012Metric_Pad1.18x1.45mm_HandSolder_C8_HandSolder | HandSolder:C_0805_2012Metric_Pad1.18x1.45mm_HandSolder_C19_HandSolder | HandSolder:C_0805_2012Metric_Pad1.18x1.45mm_HandSolder_C22_HandSolder | Sourced:Capacitor_SMD_C_0805_2012Metric | HandSolder:C_0805_2012Metric_Pad1.18x1.45mm_HandSolder_C28_HandSolder,B | F,https://www.murata.com/en-global/products/productdetail?part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 | https://www.murata.com/
C1608X7R1H104K080AA,TDK,4,C3 C7 C18 C21,100nF 50V X7R,HandSolder:C_0603_1608Metric_Pad1.08x0.95mm_HandSolder_C3_HandSolder | Sourced:Capacitor_SMD_C_0603_1608Metric | HandSolder:C_0603_1608Metric_Pad1.08x0.95mm_HandSolder_C18_HandSolder | HandSolder:C_0603_1608Metric_Pad1.08x0.95mm_HandSolder_C21_HandSolder,B | F,https://product.tdk.com/en/search/capacitor/ceramic/mlcc/inf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
GRM21BR71A475KA73L,Murata,2,C4 C6,4.7uF 10V X7R,HandSolder:C_0805_2012Metric_Pad1.18x1.45mm_HandSolder_C4_HandSolder | HandSolder:C_0805_2012Metric_Pad1.18x1.45mm_HandSolder_C6_HandSolder,B,https://www.murata.com/en-global/products/productdetail?part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
GRM21BR61C226ME44L,Murata,3,C9 C10 C33,22uF 16V X5R,HandSolder:C_0805_2012Metric_Pad1.18x1.45mm_HandSolder_C9_HandSolder | HandSolder:C_0805_2012Metric_Pad1.18x1.45mm_HandSolder_C10_HandSolder | HandSolder:C_0805_2012Metric_Pad1.18x1.45mm_HandSolder_C33_HandSolder,B,https://www.murata.com/en-global/products/productdetail?part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 | https://www.murata.com/
GRM155R71H104KE14D,Murata,9,C15 C16 C20 C27 C29 C32 C35 C36 C48,100nF 50V X7R,HandSolder:C_0402_1005Metric_Pad0.74x0.62mm_HandSolder_C15_HandSolder | HandSolder:C_0402_1005Metric_Pad0.74x0.62mm_HandSolder_C16_HandSolder | HandSolder:C_0402_1005Metric_Pad0.74x0.62mm_HandSolder_C20_HandSolder | HandSolder:C_0402_1005Metric_Pad0.74x0.62mm_HandSolder_C27_HandSolder | HandSolder:C_0402_1005Metric_Pad0.74x0.62mm_HandSolder_C29_HandSolder | HandSolder:C_0402_1005Metric_Pad0.74x0.62mm_HandSolder_C32_HandSolder | HandSolder:C_0402_1005Metric_Pad0.74x0.62mm_HandSolder_C35_HandSolder | HandSolder:C_0402_1005Metric_Pad0.74x0.62mm_HandSolder_C36_HandSolder | HandSolder:C_0402_1005Metric_Pad0.74x0.62mm_HandSolder_C48_HandSolder,B | F,https://search.murata.co.jp/Ceramy/image/img/A01X/G101/ENG/G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 | https://product.tdk.com/en/search/capacitor/ceramic/mlcc/inf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 | https://www.murata.com/
GRM188R61A106ME69D,Murata,1,C17,10uF 10V X5R 20%,HandSolder:C_0603_1608Metric_Pad1.08x0.95mm_HandSolder_C17_HandSolder,B,https://search.murata.co.jp/Ceramy/image/img/A01X/G101/ENG/G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
C1005X7R1H104K050BB,TDK,3,C24 C25 C26,100nF 50V X7R,HandSolder:C_0402_1005Metric_Pad0.74x0.62mm_HandSolder_C24_HandSolder | HandSolder:C_0402_1005Metric_Pad0.74x0.62mm_HandSolder_C25_HandSolder | HandSolder:C_0402_1005Metric_Pad0.74x0.62mm_HandSolder_C26_HandSolder,B | F,https://product.tdk.com/en/search/capacitor/ceramic/mlcc/inf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
GRM155R71H472KA01D,Murata,1,C30,4.7nF 50V X7R 10%,Sourced:C_0402_1005Metric,F,https://search.murata.co.jp/Ceramy/image/img/A01X/G101/ENG/G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
GRM1555C1H102JA01D,Murata,1,C31,1nF 50V C0G,HandSolder:C_0402_1005Metric_Pad0.74x0.62mm_HandSolder_C31_HandSolder,B,https://www.murata.com/
T520D337M006ATE025,KEMET,1,C37,330uF 6.3V polymer,HandSolder:CP_EIA-7343-31_Kemet-D_C37_HandSolder,F,https://docs.rs-online.com/885c/A700000006401849.pdf
CL05A105KP5NNNC,Samsung Electro-Mechanics,6,C38 C39 C40 C41 C42 C43,1uF 10V X5R,HandSolder:C_0402_1005Metric_Pad0.74x0.62mm_HandSolder_C38_HandSolder | HandSolder:C_0402_1005Metric_Pad0.74x0.62mm_HandSolder_C39_HandSolder | HandSolder:C_0402_1005Metric_Pad0.74x0.62mm_HandSolder_C40_HandSolder | HandSolder:C_0402_1005Metric_Pad0.74x0.62mm_HandSolder_C41_HandSolder | HandSolder:C_0402_1005Metric_Pad0.74x0.62mm_HandSolder_C42_HandSolder | HandSolder:C_0402_1005Metric_Pad0.74x0.62mm_HandSolder_C43_HandSolder,F,https://product.samsungsem.com/mlcc/CL05A105KP5NNN.do
GRM155R61A474KE15D,Murata,1,C44,470nF 10V X5R,Sourced:C_0402_1005Metric,F,https://www.murata.com/
CL10A225KP8NNNC,Samsung Electro-Mechanics,1,C45,2.2uF 10V X5R,Sourced:C_0603_1608Metric,F,https://product.samsungsem.com/mlcc/CL10A225KP8NNN.do
T530X687M006ATE010,KEMET,2,C46 C47,680uF 6.3V polymer,HandSolder:CP_EIA-7343-43_Kemet-X_C46_HandSolder | HandSolder:CP_EIA-7343-43_Kemet-X_C47_HandSolder,F,https://search.kemet.com/download/specsheet/T530X687M006ATE010
T520D477M006ATE025,KEMET,1,C50,470uF 6.3V polymer,HandSolder:CP_EIA-7343-31_Kemet-D_C50_HandSolder,B,https://www.digikey.com/en/products/detail/kemet/T520D477M00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
"PMEG2010ER,115",Nexperia,1,D1,PMEG2010ER flyback,HandSolder:D_Diode_SMD_Nexperia_CFP3_SOD-123W_D1_HandSolder,B,https://assets.nexperia.com/documents/data-sheet/PMEG2010ER.pdf
LTST-C190KRKT,Lite-On,1,D2,CHARGE LED,HandSolder:LED_0603_1608Metric_Pad1.05x0.95mm_HandSolder_D2_HandSolder,F,
TYPE-C-31-M-12,HRO,1,J1,USB-C USB2.0,HandSolder:USB_C_Receptacle_HRO_TYPE-C-31-M-12_J1_HandSolder,F,https://www.usb.org/sites/default/files/documents/usb_type-c.zip
S2B-PH-SM4-TB(LF)(SN),JST,1,J2,BATTERY DTP803040,Sourced:Connector_JST_JST_PH_S2B-PH-SM4-TB_1x02-1MP_P2.00mm_Horizontal,F,
SM08B-SRSS-TB(LF)(SN),JST,1,J3,ST7789 HARNESS,Connector_HandSolder:Connector_JST_JST_SH_SM08B-SRSS-TB_1x08_1MP_P1.00mm_Horizontal_J3_HandSolder,F,
DM3AT-SF-PEJM5,Hirose,1,J10,microSD DM3AT-SF-PEJM5,HandSolder:microSD_HC_Hirose_DM3AT-SF-PEJM5_J10_HandSolder,B,https://www.hirose.com/en/product/p/CL0609-0031-0-00
PJ-320D-4A,Korean Hroparts Elec,1,J11,3.5mm stereo output,Sourced:AUDIO-SMD_PJ-320D,B,https://www.lcsc.com/product-detail/C95562.html
XFL4020-222MEC,Coilcraft,1,L1,2.2uH XFL4020,HandSolder:Inductor_SMD_L_Coilcraft_XxL4020_L1_HandSolder,B,https://www.coilcraft.com/getmedia/50632d43-da1b-4cdb-8ab4-3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
AO3400A,Alpha & Omega Semiconductor,1,Q1,AO3400A,HandSolder:SOT-23_Handsoldering_Q1_HandSolder,B,http://www.aosmd.com/pdfs/datasheet/AO3400A.pdf
2N7002,Nexperia,2,Q2 Q4,2N7002,HandSolder:SOT-23_Handsoldering_Q2_HandSolder | HandSolder:SOT-23_Handsoldering_Q4_HandSolder,B | F,https://assets.nexperia.com/documents/data-sheet/2N7002.pdf
AO3401A,Alpha & Omega Semiconductor,1,Q3,AO3401A,HandSolder:SOT-23_Handsoldering_Q3_HandSolder,B,https://www.aosmd.com/res/data_sheets/AO3401A.pdf
RC0402FR-07100KL,Yageo,16,R1 R11 R35 R39 R40 R42 R43 R44 R49 R50 R51 R53 R56 R57 R58 R62,100k 1%,HandSolder:R_0402_1005Metric_Pad0.72x0.64mm_HandSolder_R1_HandSolder | HandSolder:R_0402_1005Metric_Pad0.72x0.64mm_HandSolder_R11_HandSolder | Sourced:Resistor_SMD_R_0402_1005Metric | HandSolder:R_0402_1005Metric_Pad0.72x0.64mm_HandSolder_R39_HandSolder | HandSolder:R_0402_1005Metric_Pad0.72x0.64mm_HandSolder_R40_HandSolder | HandSolder:R_0402_1005Metric_Pad0.72x0.64mm_HandSolder_R42_HandSolder | HandSolder:R_0402_1005Metric_Pad0.72x0.64mm_HandSolder_R43_HandSolder | HandSolder:R_0402_1005Metric_Pad0.72x0.64mm_HandSolder_R44_HandSolder | HandSolder:R_0402_1005Metric_Pad0.72x0.64mm_HandSolder_R49_HandSolder | HandSolder:R_0402_1005Metric_Pad0.72x0.64mm_HandSolder_R50_HandSolder | HandSolder:R_0402_1005Metric_Pad0.72x0.64mm_HandSolder_R51_HandSolder | HandSolder:R_0402_1005Metric_Pad0.72x0.64mm_HandSolder_R53_HandSolder | HandSolder:R_0402_1005Metric_Pad0.72x0.64mm_HandSolder_R56_HandSolder | HandSolder:R_0402_1005Metric_Pad0.72x0.64mm_HandSolder_R57_HandSolder | Sourced:R_0402_1005Metric | HandSolder:R_0402_1005Metric_Pad0.72x0.64mm_HandSolder_R62_HandSolder,B | F,https://www.yageo.com/en/Product/Index/RC | https://www.yageo.com/
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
